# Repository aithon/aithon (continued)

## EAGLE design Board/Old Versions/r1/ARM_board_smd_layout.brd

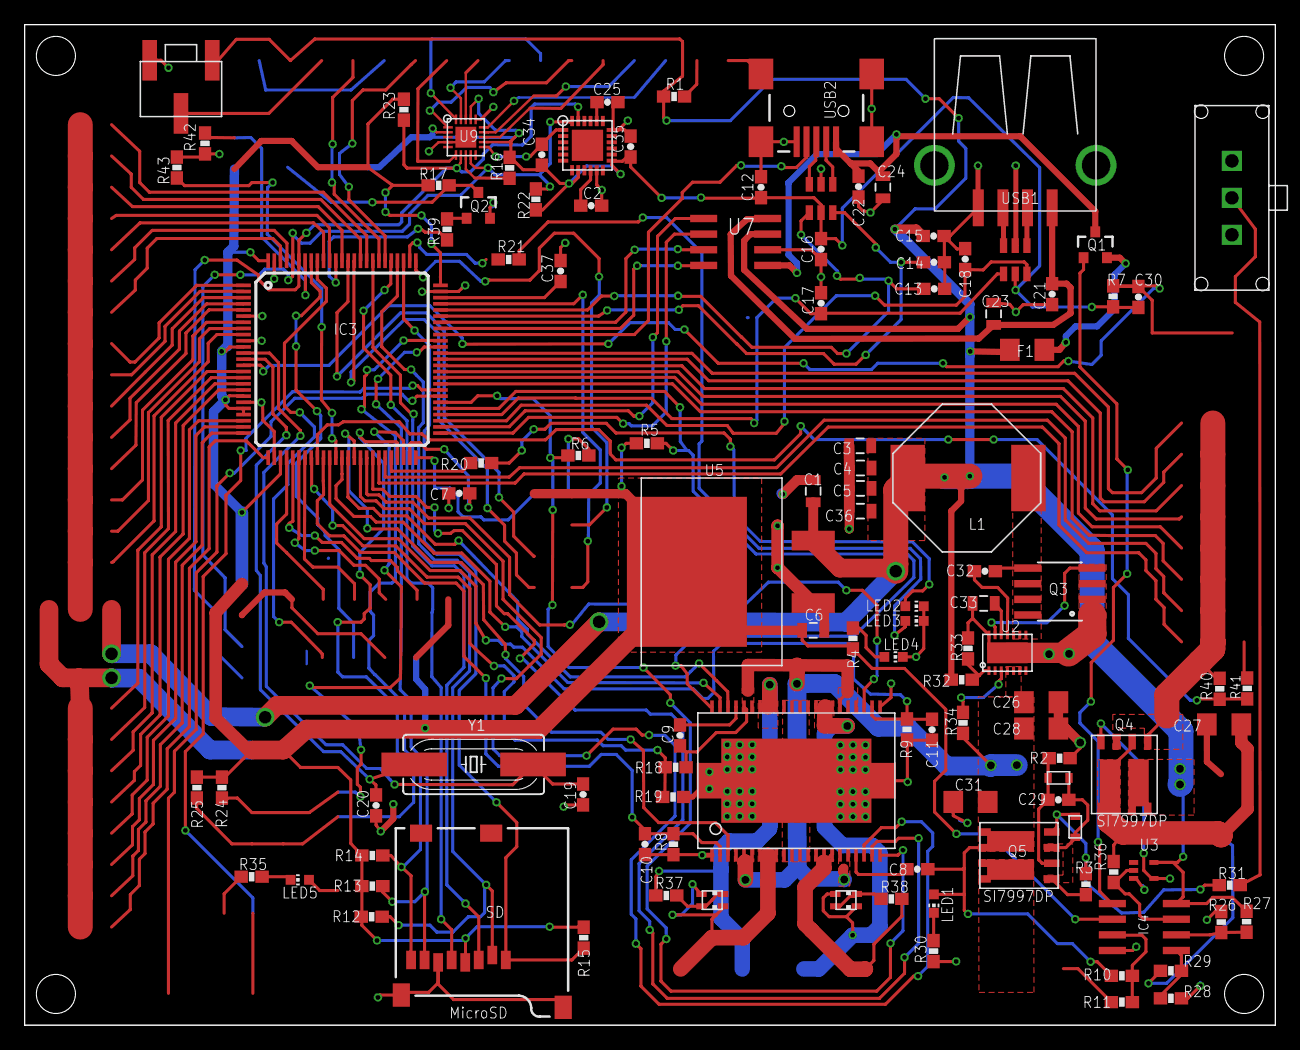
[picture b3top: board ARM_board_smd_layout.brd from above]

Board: 2 copper layers, 101.6 x 81.3 mm, 113 parts (0 on the bottom side), 88 nets.

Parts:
C1, C6, C23, C24, C33: 10u; 0805
C2, C8, C9, C12, C15, C16, C21, C22, C29: 0.1u; 0603-CAP
C3, C4, C5, C36: 22u; 0805
C7, C37: 2.2u; 0603-CAP
C10, C11, C32: 1u; 0603-CAP
C13, C14, C17, C18: 47p; 0603-CAP
C19, C20: 22p; 0603-CAP
C25: 2.2n; 0603-CAP
C26, C28: 10u; 1206
C27, C31: 22u; 1206
C30, C35: 10n; 0603-CAP
C34: 0.1uF; 0603-CAP
F1: POLYFUSE; 1206
IC3: STM32F407VET; TQFP100
IC4: LM358D; SO08
L1: 2.7u; INDUCTOR
LED1, LED4: RED; CHIP-LED0603
LED2, LED3, LED5: YELLOW; CHIP-LED0603
LED6, LED7: LED_R/G; LED-0606
POT: 10K; POT
Q1: Si2301; SOT23-3
Q2: BC817; SOT23-3
Q3: FDS6670AS; SO08
Q4, Q5: SI7997DP; POWERPAK
R1: 10; 0603-RES
R2, R3, R34: 100k; 0603-RES
R4, R8, R9, R20, R21, R35: 220; 0603-RES
R5, R6, R7, R10, R11, R16, R19, R22, R23, R24, R25, R26, R28, R31, R36, R41, R42, R43: 10k; 0603-RES
R12, R13, R14, R15: 33k; 0603-RES
R17, R39: 1k; 0603-RES
R18, R32, R40: 93.1k; 0603-RES
R27, R29: 39k; 0603-RES
R30, R37, R38: 2k; 0603-RES
R33: 18k; 0603-RES
SD: USD-SOCKETNEW; MICRO-SD-SOCKET-PP
SW1: SW
U1: MC33932; HSOP44
U2: RT7259; WDFN-14L
U3: NC7SZU04; SC70
U4: MPU-6050; QFN-24_IMU
U5: LD1086; D2PAK
U6, U8: USBLC6-2; SOT23-6L
U7: LM3526; SO08
U9: SX1505; QFN-UT-20
USB1: USB-A-S
USB2: USB-MINIB-5PIN; USB-MINIB
Y1: 24MHz; HC49UP
ZD1, ZD2: 15V; 0603

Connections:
5V: C1.1, C3.1, C4.1, C5.1, C15.1, C36.1, F1.2, IC4.8, L1.P$2, POT.1, Q4.7, Q4.8, Q4.9, R1.2, R27.2, R32.2, U3.5, U5.VIN, U7.7
+3V3: C6.1, C12.1, C16.1, C30.1, C34.1, C35.1, IC3.11, IC3.19, IC3.21, IC3.22, IC3.28, IC3.50, IC3.75, IC3.100, IC4.2, R4.2, R5.2, R6.1, R7.2, R12.1, R13.1, R14.1, R15.2, R16.2, R17.1, R22.2, R23.2, R24.2, R25.2, SD.4, U4.8, U4.13, U5.VOUT, U6.P$5, U8.P$5, U9.P$7, U9.P$14, U9.P$17
BAT_SENSE: IC3.33, R18.2, R19.1
BOOT0: IC3.94, R42.2
BOOT1: IC3.37, R43.2
BUZZER: IC3.89, R39.1
GND: C1.2, C2.2, C3.2, C4.2, C5.2, C6.2, C7.1, C10.2, C11.2, C12.2, C13.2, C14.2, C15.2, C16.2, C17.2, C18.2, C19.2, C20.1, C21.2, C22.1, C23.2, C24.1, C25.2, C26.2, C27.2, C28.2, C31.2, C33.1, C34.2, C35.2, C36.2, C37.2, IC3.6, IC3.10, IC3.20, IC3.27, IC3.74, IC3.99, IC4.4, LED2.C, LED3.C, LED4.C, POT.3, Q2.2, Q3.1, Q3.2, Q3.3, R2.2, R8.1, R9.1, R11.1, R19.2, R26.1, R28.2, R30.1, R33.1, R35.1, R41.2, R42.1, R43.1, SD.6, SD.GND1, SD.GND3, SW1.P$2, U1.P$1, U1.P$10, U1.P$11, U1.P$12, U1.P$13, U1.P$23, U1.P$32, U1.P$33, U1.P$34, U1.P$35, U1.P$45, U1.P$46, U1.P$47, U2.14, U2.P$1, U3.3, U4.1, U4.9, U4.11, U4.18, U5.GND, U6.P$2, U7.6, U8.P$2, U9.P$8, U9.P$12, U9.P$18, U9.P$21, USB1.GND, USB1.GND@1, USB1.GND@2, USB2.GND, USB2.MTN1, USB2.MTN2, USB2.MTN3, USB2.MTN4
I2C1_SCL: IC3.95, R23.1, U4.23, U9.P$4
I2C1_SDA: IC3.96, R22.1, U4.24, U9.P$2
I2C2_SCL/USART3_TX: IC3.47, R25.1
I2C2_SDA/USART3_RX: IC3.48, R24.1
LED0: IC3.46, R20.2
M1_A: IC3.38, U1.P$43
M1_B: IC3.39, U1.P$42
M1_EN: IC3.40, U1.P$3
M1_FAULT: IC3.55, R5.1, U1.P$44
M1_SENSE: C10.1, IC3.35, R8.2, U1.P$2
M2_A: IC3.41, U1.P$20
M2_B: IC3.43, U1.P$21
M2_EN: IC3.42, U1.P$25
M2_FAULT: IC3.56, R6.2, U1.P$22
M2_SENSE: C11.1, IC3.36, R9.2, U1.P$24
MPOWER: C8.1, C9.2, C26.1, C28.1, C31.1, LED1.A, Q5.5, Q5.6, Q5.10, R10.2, R18.1, R34.2, U1.P$4, U1.P$5, U1.P$6, U1.P$17, U1.P$18, U1.P$26, U1.P$27, U1.P$28, U1.P$39, U1.P$40, U2.4, U2.5, U2.6
unnamed: Q5.7, Q5.8, Q5.9
unnamed: C29.2, Q5.2, R2.1, ZD1.P$1
unnamed: C25.1, U4.20
unnamed: C37.1, IC3.73
unnamed: IC4.3, R10.1, R11.2
unnamed: C2.1, U4.10
unnamed: U8.P$1, USB2.D-
unnamed: U8.P$3, USB2.D+
unnamed: LED4.A, R4.1
unnamed: C32.2, L1.P$1, Q3.5, Q3.6, Q3.7, Q3.8, U2.8, U2.9, U2.10
unnamed: C7.2, IC3.49
unnamed: IC4.5, R28.1, R29.2
unnamed: U6.P$3, USB1.D+
unnamed: IC4.1, Q1.1
unnamed: F1.1, Q1.2
unnamed: U6.P$1, USB1.D-
unnamed: R32.1, R33.2, U2.1
unnamed: LED5.C, R35.2
unnamed: C33.2, U2.12
unnamed: C21.1, C23.1, U7.8, USB1.VBUS
unnamed: R31.2, SW1.P$1
unnamed: C29.1, Q5.1, Q5.3, R3.2, ZD1.P$2, ZD2.P$2
unnamed: C32.1, U2.11
unnamed: IC4.6, R26.2, R27.1
unnamed: IC4.7, R36.1, U3.2
unnamed: Q2.3, R17.2
unnamed: Q4.4, U3.4
unnamed: Q3.4, U2.13
unnamed: LED2.A, R20.1
unnamed: LED3.A, R21.1
unnamed: R34.1, U2.3
unnamed: C19.1, IC3.12, Y1.2
unnamed: C20.2, IC3.13, Y1.1
unnamed: LED1.C, R30.2
unnamed: C9.1, U1.P$41
unnamed: C8.2, U1.P$19
unnamed: LED6.1, LED6.4, R37.2
unnamed: LED7.1, LED7.4, R38.2
unnamed: Q2.1, R39.2
unnamed: Q5.4, R3.1, R31.1, ZD2.P$1
unnamed: R16.1, U9.P$1
OTG_FS_DM: C14.1, IC3.70, U8.P$6
OTG_FS_DP: C13.1, IC3.71, U8.P$4
OTG_FS_FAULT: IC3.69, U7.3
OTG_FS_ID: IC3.67, USB2.ID
OTG_FS_VBUS: IC3.68, U7.4
OTG_HS_DM: C18.1, IC3.53, U6.P$6
OTG_HS_DP: C17.1, IC3.54, U6.P$4
OTG_HS_FAULT: IC3.51, U7.2
OTG_HS_VBUS: IC3.52, U7.1
OUT1: LED6.2, LED6.3, U1.P$7, U1.P$8, U1.P$9
OUT2: R37.1, U1.P$36, U1.P$37, U1.P$38
OUT3: LED7.2, LED7.3, U1.P$29, U1.P$30, U1.P$31
OUT4: R38.1, U1.P$14, U1.P$15, U1.P$16
RAW_SPWR: C27.1, Q4.2, Q4.5, Q4.6, Q4.10, R29.1, R36.2
RESET: C30.2, IC3.14, R7.1
SDIO_CK: IC3.80, SD.5
SDIO_CMD: IC3.83, SD.3
SDIO_D0: IC3.65, R13.2, SD.7
SDIO_D1: IC3.66, R14.2, SD.8
SDIO_D2: IC3.78, R15.1, SD.1
SDIO_D3: IC3.79, R12.2, SD.2
SERVO_SENSE: IC3.34, R40.2, R41.1
SPWR: Q4.1, Q4.3, R40.1
USB_5V: C22.2, C24.2, Q1.3, U7.5, USB2.VBUS

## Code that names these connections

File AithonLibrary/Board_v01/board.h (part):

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
/*
 * Port A setup:
 * PA0  - GPIOA_ANALOG3             (analog input)
 * PA1  - GPIOA_ANALOG2             (analog input)
 * PA2  - GPIOA_ANALOG1             (analog input)
 * PA3  - GPIOA_ANALOG0             (analog input)
 * PA4  - GPIOA_BUZZER              (output pulldown)
 * PA5  - GPIOA_SPI1_SCK            (alternate function 5)
 * PA6  - GPIOA_SPI1_MISO           (alternate function 5)
 * PA7  - GPIOA_SPI1_MOSI           (alternate function 5)
 * PA8  - GPIOA_LCD_DATA            (output pushpull)
 * PA9  - GPIOA_USB_DEV_5V          (input pulldown)
 * PA10 - GPIOA_LCD_CLK             (output pushpull)
 * PA11 - GPIOA_USB_DEV_DM          (alternate function 10)
 * PA12 - GPIOA_USB_DEV_DP          (alternate function 10)
 * PA13 - GPIOA_SWDIO               (alternate function 0 / pulldown)
 * PA14 - GPIOA_SWCLK               (alternate function 0 / pullup)
 * PA15 - GPIOA_SPI1_NSS            (alternate function 5)
 */
#define VAL_GPIOA_MODER    (PIN_MODE_ANALOG(GPIOA_ANALOG3) | \
                            PIN_MODE_ANALOG(GPIOA_ANALOG2) | \
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
/*
 * Port B setup:
 * PB0  - GPIOB_ANALOG9             (analog input)
 * PB1  - GPIOB_ANALOG8             (analog input)
 * PB2  - GPIOB_BOOT1               (input floating)
 * PB3  - GPIOB_DIGITAL12           (input floating)
 * PB4  - GPIOB_DIGITAL11           (input floating)
 * PB5  - GPIOB_DIGITAL10           (input floating)
 * PB6  - GPIOB_USART1_TX           (alternate function 7)
 * PB7  - GPIOB_USART1_RX           (alternate function 7)
 * PB8  - GPIOB_I2C1_SCL            (alternate function 4)
 * PB9  - GPIOB_I2C1_SDA            (alternate function 4)
 * PB10 - GPIOB_I2C2_SCL_USART3_TX  (alternate function 7)
 * PB11 - GPIOB_I2C2_SDA_USART3_RX  (alternate function 7)
 * PB12 - GPIOB_USB_HOST_FAULT      (input pullup)
 * PB13 - GPIOB_USB_HOST_EN         (alternate function 10)
 * PB14 - GPIOB_USB_HOST_DM         (alternate function 10)
 * PB15 - GPIOB_USB_HOST_DP         (alternate function 10)
 */
#define VAL_GPIOB_MODER    (PIN_MODE_ANALOG(GPIOB_ANALOG9) | \
                            PIN_MODE_ANALOG(GPIOB_ANALOG8) | \
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
/*
 * Port C setup:
 * PC0  - GPIOC_ANALOG7             (analog input)
 * PC1  - GPIOC_ANALOG6             (analog input)
 * PC2  - GPIOC_ANALOG5             (analog input)
 * PC3  - GPIOC_ANALOG4             (analog input)
 * PC4  - GPIOC_BAT_SENSE           (analog input)
 * PC5  - GPIOC_SERVO_SENSE         (analog input)
 * PC6  - GPIOC_SERVO4              (alternate function 3)
 * PC7  - GPIOC_SERVO5              (alternate function 3)
 * PC8  - GPIOC_SERVO6              (alternate function 3)
 * PC9  - GPIOC_SERVO7              (alternate function 3)
 * PC10 - GPIOC_SPI3_SCK            (alternate function 6)
 * PC11 - GPIOC_SPI3_MISO           (alternate function 6)
 * PC12 - GPIOC_SPI3_MOSI           (alternate function 6)
 * PC13 - GPIOC_DIGITAL2            (input floating)
 * PC14 - GPIOC_DIGITAL1            (input floating)
 * PC15 - GPIOC_DIGITAL0            (input floating)
 */
#define VAL_GPIOC_MODER    (PIN_MODE_ANALOG(GPIOC_ANALOG7) | \
                            PIN_MODE_ANALOG(GPIOC_ANALOG6) | \
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
/*
 * Port D setup:
 * PD0  - GPIOD_LCD_E               (output pushpull)
 * PD1  - GPIOD_LCD_RS              (output pushpull)
 * PD2  - GPIOD_SPI3_NSS            (output pushpull)
 * PD3  - GPIOD_DIGITAL14           (input floating)
 * PD4  - GPIOD_LED1                (output pushpull)
 * PD5  - GPIOD_USART2_TX           (alternate function 7)
 * PD6  - GPIOD_USART2_RX           (alternate function 7)
 * PD7  - GPIOD_DIGITAL13           (input floating)
 * PD8  - GPIOD_MOTOR0_FAULT        (input pullup)
 * PD9  - GPIOD_MOTOR1_FAULT        (input pullup)
 * PD10 - GPIOD_BTN0                (input pullup)
 * PD11 - GPIOD_BTN1                (input pullup)
 * PD12 - GPIOD_SERVO0              (alternate function 2)
 * PD13 - GPIOD_SERVO1              (alternate function 2)
 * PD14 - GPIOD_SERVO2              (alternate function 2)
 * PD15 - GPIOD_SERVO3              (alternate function 2)
 */
#define VAL_GPIOD_MODER    (PIN_MODE_OUTPUT(GPIOD_LCD_E) | \
                            PIN_MODE_OUTPUT(GPIOD_LCD_RS) | \
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
/*
 * Port E setup.
 * PE0  - GPIOE_DIGITAL9            (input floating)
 * PE1  - GPIOE_DIGITAL8            (input floating)
 * PE2  - GPIOE_DIGITAL7            (input floating)
 * PE3  - GPIOE_DIGITAL6            (input floating)
 * PE4  - GPIOE_DIGITAL5            (input floating)
 * PE5  - GPIOE_DIGITAL4            (input floating)
 * PE6  - GPIOE_DIGITAL3            (input floating)
 * PE7  - GPIOE_MOTOR0_A            (output push-pull)
 * PE8  - GPIOE_MOTOR0_B            (output push-pull)
 * PE9  - GPIOE_MOTOR0_EN           (alternate function 1)
 * PE10 - GPIOE_MOTOR1_A            (output push-pull)
 * PE11 - GPIOE_MOTOR1_EN           (alternate function 1)
 * PE12 - GPIOE_MOTOR1_B            (output push-pull)
 * PE13 - GPIOE_DIGITAL15           (input floating)
 * PE14 - GPIOE_DIGITAL16           (input floating)
 * PE15 - GPIOE_LED0                (output push-pull)
 */
#define VAL_GPIOE_MODER    (PIN_MODE_INPUT(GPIOE_DIGITAL9) | \
                            PIN_MODE_INPUT(GPIOE_DIGITAL8) | \
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
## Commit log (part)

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2013-10-24 initial checkin of plugin
2013-10-24 modified readme
2013-10-25 Organized and added files from old git repository.
2013-10-25 Coding Style Guidelines
2013-10-27 include unistd.h for Linux compile
2013-10-28 Rewrote bootloader from scratch to be more robust. Need to put get USB programming back in and working still as well as clean up error conditions and remove some test code.
2013-10-28 Rewrite programmer to be more robust. Still need to fully implement error handling and make the console output prettier.
2013-10-30 fix compiler warning
2013-10-30 created directory to automate jEdit builds
2013-10-31 builds Mac installer with Aithon library included
2013-10-31 added README instructions for building
2013-10-31 initial check in of Windows files
2013-10-31 moved jedit installer directory
2013-10-31 Added aithon logo/changed button sizes
2013-10-31 fix path to Aithon library
2013-10-31 initial check in Aithon splash image
2013-10-31 speed up compilation process
2013-11-02 Compiles on click and prints output to console
    Uses makefile in Project Templates folder - still needs to be more
    general. Directory to makefile hardcoded.
2013-11-05 remove backup files
2013-11-05 remove HTML formatting
2013-11-05 changed paths for Windows
2013-11-05 add Aithon.jar to installer
2013-11-05 fix installer path error
2013-11-06 Added "command" parameter which currently supports "detect" and "program" for detecting the COM port and programming the board respectively. The program command will also auto-detect the COM port.
2013-11-07 make OS specific directories
2013-11-07 add Linux binary versions of programmer
2013-11-07 Added error printing for compiling
    Cleaned up some code and comments as well
2013-11-07 added ProjectTemplate to default install package
2013-11-08 Added options for compiler, library, and programmer paths
    Using upload button to test - prints out current paths entered
2013-11-08 Only set default option paths if not set
    Checks if user has entered a path before finding a default path
2013-11-11 ProjectTemplate directory is found through property
    If library path is entered, the ProjectTemplate directory can be found
    using that location
2013-11-13 Removed reset thread from aithon library. The USB device driver is now always active. Updated USB CDC implementation and added auto-reset functionality (for programming). Added some code which is use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
2013-11-13 Updated programmer to do auto-resetting as well as some other changes in the programming architecture.
2013-11-14 Messed around with Makefiles in order to simplify the one which resides in the project directory.
2013-11-15 Added support for programming over UART to the uploader. Also added an auto-reset mechanism to the library for UART programming. Cleaned up the makefiles a bit more.
2013-11-16 Enabled SPI3 for the microSD card. Changed the project template slightly.
2013-11-17 Added FATFS library. Verified microSD socket functionality and added aiSDInit() function for initializing an inserted card and the FATFS filesystem.
2013-11-18 -Added -j flag to makefile. -Moved application to sector 4. -Added EEPROM library which emulates EEPROM using sectors 2 and 3 of FLASH (16k each) to provide 256 EEPROM addresses (each addressing 16 b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
2013-11-18 Compiles currently opened file using Makefile in ProjectTemplate folder
    Tested by adding a main.c copy into different location. Changed Makefile
    slightly to fix pathing/compiling issues.
2013-11-20 Changed backslashes to forward for Linux/Mac
    Also did some cleaning up of code
2013-11-21 Backed out change which added -j flag in makefile.
2013-11-21 Fixed wrongly reverted files.
2013-12-10 Cleaned up Aithon library function names and code.
2013-12-12 Automatically set Library and Programmer directories
    Sets to the AithonLibrary in the install directory. Still issues with
    compiling within this location, though.
2014-01-15 Updated to ChibiOS 2.6.2.
2014-01-15 Missed some files with the last commit.
2014-01-16 Updated bootloader to keep LED0 on and blink LED1 quickly. Fixed typo's and minor style issues in bootloader and library code. Added initial board testing code.
2014-01-16 Added Board folder for new v0.1 boards. Added library support for new boards while maintaining rev4 support. Added temporary field to user-application Makefiles for specifying the board revision. Add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
2014-01-19 Fixed typo in delayMs which was sleeping for microseconds instead of milliseconds. Fixed I2C1 pins to be open drain. Added 1us delay to LCD code. Removed all rev4 code from Aithon Library.
2014-01-19 Moved Eagle files from dropbox to new "Board" directory in Github.
2014-01-19 Added green box 30mil inside the board outline and moved all traces within the line. Removed the extra space that was added around the board for the previous revision. Removed the zener diodes for no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
2014-01-19 Fixed parts that were too close together.
2014-01-20 Changed servo power select resistors.
2014-01-20 changed to usleep for Mac/Linux
2014-01-21 Added "program" target to makefile.
2014-01-21 Removed comment from 'make program' which was getting printed out.
2014-01-21 Added basic SD card tests to Tester program.
2014-01-23 Added "-d" option to uploader and compiled new .exe for windows.
2014-01-24 fix to make servo 0 work
2014-01-24 Compiled new programmer for windows.
2014-01-24 Recompiled again.
2014-01-26 Compiled new version for windows.
2014-01-26 Missed some qt file changes in the last commit.
2014-01-26 Fixed typos in board.h file.
2014-01-26 Fixed AFR configuration for motors.
2014-01-26 Applied fixes for ChibiOS Bugs 457 and 458.
2014-01-26 Increase bootloader timeout to 30 seconds.
2014-01-27 Starting updating the schematic for the new switching regulator.
2014-01-28 Made changes to switching regulator section of schematic.
2014-01-30 Created parts for Issue 44
2014-01-30 Placed both of the dual mosfets on the schematic.
    They replaced U17 & U18 were replaced with U17 (dual-mosfet).
    They replaced U19 & U20 were replaced with U19 (dual-mosfet).
2014-01-31 Cleaned up Dual-Mosfet symbol on schematic
2014-02-01 Cleaned up old Testing folder. Cleaned up project template.
2014-02-01 Changed the reset sequence and tweaked how the uploader waits for the board to reset to be faster. Cleared out the project template main.c file. Built new uploader for windows.
2014-02-02 Cleaned out generated files from the current board directory. Finished laying out new regulator and all other schematic changes so far.
2014-02-02 Tweaked servo traces to widen 5V trace for servo power.
2014-02-02 Added more debug to getCOMPort() and now calling it after we check for the -d flag.
2014-02-03 Build a static executable for Linux
2014-02-03 Got initial programming working on linux.
2014-02-03 Added missing changes from previous commit
2014-02-03 Removed compiled files from previous commit
2014-02-03 Removed more compiled files
2014-02-06 Cleaned up bottom-left of the board. Moved the power LED above the switching section. Flipped the power switch around.
2014-02-13 More tweaks to layout.
2014-02-13 Replaced LSM330DLC with LSM330 and re-added horse
    LSM330 replaced LSM330DLC.
    Re-added horse logo to board.
    Moved labels in UART1 box down slightly.
2014-02-15 Removed excess motor pin initialization.
2014-02-15 Updated board definitions for motor pins.
2014-02-16 Changed how the erase sequence works in the bootloader and the uploader to be faster.
2014-02-16 added the date to the bootloader
2014-02-16 Added date for windows as well. Fixed the issue with motors going in opposite directions. Removed unnecessary lcd_cursor() calls in bootloader.
2014-02-16 fixed typo on date
2014-02-17 stores user code in user_objs
2014-02-17 Added LD1117 linear regulator to r_cubed library.
2014-02-17 modified linking script to use usertext
2014-02-17 Updated for linux
2014-02-17 Updated exe for windows.
2014-02-17 separate .rodata for OS and user application
2014-02-17 Added 3.3V LDO for USB power to the schematic.
2014-02-17 changed directory name
2014-02-17 fix data placement error
2014-02-17 add bss sections
2014-02-17 split RAM and bss sections
2014-02-17 Added more debug prints to the uploader.
2014-02-17 move interrupt vectors to application section
2014-02-18 Added some delays and updated uploader on linux.
2014-02-18 Started on a test mode of the uploader. Cleaned up the Aithon.mk targets.
2014-02-18 Added more debug and retries.
2014-02-18 Added more debugging.
2014-02-18 Added more retries and debugging.
2014-02-18 Forcing the COM port to write one byte at a time.
2014-02-18 Reverted changes to the project template.
2014-02-18 Removed LibSerial. Recompiled .exe for windows.
2014-02-18 Rebuilt executable for linux.
2014-02-18 Moved serial functions to the top of the file.
2014-02-18 Switched Q3 around. Minor layout tweaks.
2014-02-18 added .h files and modified code to compile
2014-02-18 Addressed switching regulator comments.
2014-02-18 code compiles with avrdude functions
2014-02-18 changed to open port
2014-02-18 first working programming with avrdude functions
2014-02-19 Cleaned up the layout.
2014-02-19 programs every other time
2014-02-19 adjusted delays
2014-02-19 can program every time, still ioctl errors
2014-02-20 added #ifdefs to separate the avrdude code
2014-02-20 Fixed the size of the 680uF capacitors. Added new voltage divider on SHDWN pin of switching controller.
2014-02-20 Went through the size of all the passives.
2014-02-20 Missed a file in previous commit.
2014-02-20 ifdefs for Mac and Windows
2014-02-20 ifdef file descriptor
2014-02-21 working bootloader update
2014-02-21 update comments
2014-02-21 added README
2014-02-21 do not update already updated bootloader
2014-02-22 initial LCD scrolling library
2014-02-22 added locking to scroll thread, updated bootloader screen (no options implemented yet)
2014-02-22 Fixed lcd_cursor() prototype.
2014-02-22 Moved the scroll_lcd code into the lcd file and started cleaning it up to match the library style.
2014-02-22 more ifdefs for Mac
2014-02-23 testing modes
2014-02-23 Revert "merge of uploader from avrdude_serial branch"
    This reverts commit 47851d11dbe28de0425b45e99b2684e0efe1f95b.
2014-02-23 Revert "initial LCD scrolling library"
    This reverts commit 92c32e8b69a54e96a503ed6309524d237071e856.
2014-02-23 clean up sample code
2014-02-23 add initial pause before scrolling
2014-02-23 added bootloader servo test
2014-02-23 added bootloader motor test
2014-02-24 beginnings of bootloader terminal mode
2014-02-24 added motor, servo, and analog to terminal mode
2014-02-25 Added more capacitors to the gyro.
2014-02-25 Cleaned up the layout around the gyro a bit.
2014-02-25 fix for Window compilation
2014-02-25 modified windows fix
2014-02-25 fix to make ProjectTemplate portable
2014-02-25 change library path
2014-02-26 Made some minor tweaks to the schematic and layout while creating the BOM.
2014-02-26 added new demo linker script
2014-02-26 modified flash address for demo mode
2014-02-26 remove build files
2014-02-26 change demo program starting address
2014-02-26 change bootloader flash size
2014-02-26 removed old pre-built Mac programmer binary
2014-02-27 removed unnecessary build support directory
2014-02-27 updated svn repository
2014-02-27 Made tweaks to schematic / layout.
2014-02-27 Fixed battery / servo voltage enum.
2014-02-27 moved scrolling display code into demo program
2014-02-27 working Mac compile button
2014-02-27 updated Mac AithonProgrammer install links
2014-02-27 added action for compile command button
2014-02-28 removed Mac default programmer
2014-02-28 added compile and detecion option to plugin
2014-03-01 Changed a bunch of the #defines in the flash code to const arrays. Cleaned up some code. Fixed issue with making from scratch on Windows.
2014-03-01 Shortened delay to start the program after uploading a new one.
2014-03-01 Renamed last section of flash and flash start variable.
2014-03-01 Added sanity check to __late_init() and cleaned up makefile a bit.
2014-03-01 Fixed some bugs in the bootloader / flash code and generally cleaned it up. Recompiled new exe for the windows uploader.
